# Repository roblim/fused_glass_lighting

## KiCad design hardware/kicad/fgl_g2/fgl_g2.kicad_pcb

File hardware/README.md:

# hardware/

KiCad projects and the scripts that generate and check them. Start with [`../docs/hardware.md`](../docs/hardware.md). For the current board, Rev G2, the decisions are in [`../docs/g2_decisions.md`](../docs/g2_decisions.md).

## Layout

| Path | What |
|---|---|
| `kicad/fgl_g2/` | **Rev G2 controller (current):** `fgl_g2.kicad_pro`/`.kicad_sch`/`.kicad_pcb` (laid out, zones filled), `fgl_g2.pdf`, `fgl_g2.net`, `ERC.rpt`, `DRC.rpt`, `verification.txt`, `bom.csv`, `bom_jlcpcb.csv`, `fgl_g2_layout.png`, `fgl_g2_3d.png`, `fgl_g2_assembly.pdf` (assembly drawing), `fgl.kicad_sym`, `fgl.pretty/` (JILN JL212R port block), and `jlcpcb/` (gerber zip, a BOM + CPL pair for each port variant, DEGSON and JILN, `make_cpl.py`: pad-centre positions and per-LCSC-part rotations checked against JLCPCB's preview) |
| `kicad/fgl_g1/` | Rev G1 controller, superseded 2026-10-23 (KiCad 9, laid out, JLCPCB files in `jlcpcb/`). Kept for reference; don't order |
| `kicad/fgl_rev_f/` | Rev F prototype as built (documentation only; no footprints) |
| `tools/kgen.py` | Small KiCad 7-format schematic writer used by the generators. Supports off-board symbols and per-pin stub lengths |
| `tools/symlib.py` | Project symbols: XIAO ESP32C3, TPS61500, filament port, pot+switch header, LD1500SB, PD trigger, LD2410S, radar and pot headers |
| `tools/gen_g2.py` | Draws the G2 schematic (first version; see Source of truth) |
| `tools/gen_g2_footprints.py` | Writes the Degson terminal footprint into `kicad/fgl_g2/fgl.pretty/` |
| `tools/sepic_design.py` | G2 SEPIC checks (method from TI SLVA904) |
| `tools/gen_g1.py` | Drew the first G1 schematic. Retired |
| `tools/gen_rev_f.py` | Generates the Rev F schematic |
| `tools/g2_expected.py`, `tools/g1_expected.py`, `tools/rev_f_expected.py` | Design intent, written by hand, independent of the generators |
| `tools/verify_pcb.py` | Checks every pad's net on a `.kicad_pcb` against the expected module (`verify_pcb.py board g2_expected`) |
| `tools/verify_netlist.py` | Compares KiCad's exported netlist (s-expression or XML) with the expected one. Also checks no-connects, power sources, footprint pads and BOM fields |
| `tools/schlib.py`, `tools/redraw_g2_sepic.py`, `tools/tidy_g2_labels.py` | Schematic text helpers (pin positions, items in a region, wire/label builders) and the 2026-10-28 clean-up after Flux's review: section 2 (SEPIC) redrawn with wires, label overlaps at JP1/JP2/VBUS_IN/F1/Q2 cleared. Connectivity unchanged |
| `tools/set_datasheets.py` | Fills the Datasheet field of every purchased G2 part (schematic and board) with a direct PDF link, by LCSC number |
| `tools/make_pads_netlist.py` | PADS-PCB netlist (`fgl_g2_pads.asc`) from the KiCad netlist, for tools that don't read KiCad's own format (Pinscope). Same layout as KiCad's PADS export; single-pin nets (unconnected pins) are left out |
| `tools/make_bom.py` | `bom.csv` and `bom_jlcpcb.csv` from the netlist (`make_bom.py net outdir g2_expected` for G2) |
| `tools/power_model.py` | Power and runtime model for Rev F, G1 and G2, inputs listed with sources |
| `tools/layout_g2b/` | Scripts that produced the 90 × 60 mm G2 layout (D19; reference only, the `.kicad_pcb` is the master) |
| `tools/layout_g2/` | Scripts that produced the first, 74 × 58 mm G2 layout (D15; reference only) |
| `tools/make_port_step.py` | Simplified 3D model of the JL212R / DG212R port block (same size) |
| `tools/layout_g1/` | Scripts that produced the G1 layout (reference only) |
| `tools/build.sh` | Exports, verifies (netlist, and the G2 PCB) and rebuilds the BOMs for G2 and G1; runs G2 DRC; regenerates and verifies Rev F |

## Source of truth

**G2:** `kicad/fgl_g2/fgl_g2.kicad_sch` was generated by `gen_g2.py` on 2026-10-23, then saved in KiCad 9.0.7. It is now the master, and `gen_g2.py` refuses to overwrite it unless run with `--force`. Checks:

- **Netlist:** passes `verify_netlist.py` against `g2_expected.py`: 42 nets, 177 connections, 9 no-connects, 74 parts (after the Oct 28 relayout with R29, D19). Mutation tests (JP1 pins 1 and 3 swapped; JP2 pins 1 and 2 swapped; R29 pins swapped) fail as they should.
- **ERC (KiCad 9):** 0 errors. Run through the KiCad MCP's CLI (last on Oct 28) it also lists 69 "footprint not found in library" warnings, one per stock footprint, because that CLI looks for the stock libraries in the wrong folder; `build.sh` with `KiCad.app`'s CLI should give 0 warnings.
- **PCB:** 90 × 60 mm, laid out with `tools/layout_g2b/` (D19 in `g2_decisions.md`; the first 74 × 58 mm layout came from `tools/layout_g2/`, D15). 3D models: the makers' files in `kicad/fgl_g2/3dmodels/`, attached by `tools/set_3d_models.py`. With zones filled, DRC gives 0 errors and 0 unconnected pads. `verify_pcb.py` passes (186 pads, 69 footprints): every pad's net on the board matches `g2_expected.py`.

**G1:** `kicad/fgl_g1/` is frozen as of 2026-10-22, and `gen_g1.py` is retired.

**Rev F:** documentation only. It is still generated by `gen_rev_f.py`.

## Checking after an edit

```
hardware/tools/build.sh
```

This uses KiCad 9's `kicad-cli` from `KiCad.app` (override with `KICAD_CLI`). For G2 and G1 it:

- exports the netlist and PDF
- runs ERC into `ERC.rpt`
- checks the netlist against the expected module
- rewrites the BOMs

It never regenerates G2 or G1.

When you change a circuit, update its `*_expected.py` to match. The verifier will fail until you do. That's deliberate: it is a second, independent statement of what the board should be.

Library paths are found automatically on macOS (`KiCad.app`) and Linux (`/usr/share/kicad`). Override them with `KICAD_SYMBOL_DIR` and `KICAD_FOOTPRINT_DIR`. The G2 TPS61500 footprint (`Package_SO:Texas_HTSSOP-14-1EP…`) exists only in KiCad 9 libraries. On older libraries the verifier uses the pad list recorded in `g2_expected.EXTERNAL_PADS`.

## Not done yet (G2)

These are listed with detail in [`../docs/g2_decisions.md`](../docs/g2_decisions.md#open-items-before-ordering-g2):

- **JLCPCB placement preview:** check every part in the checklist in `docs/hardware.md` (ordering step 3).
- **Header pins against the 5 mm sockets:** 6 mm pins may stop the modules about 2 mm high (D15).
- **Fuse stock.**
- **G2 firmware build.** `src/main.c` has the G2 build (`pio run -e seeed_xiao_esp32c3_g2`), but it has only been compile-checked against the ESP-IDF headers. Build and flash it with PlatformIO. Setup mode, blink codes, keep-alive while lit and the radar UART configuration are still to do.

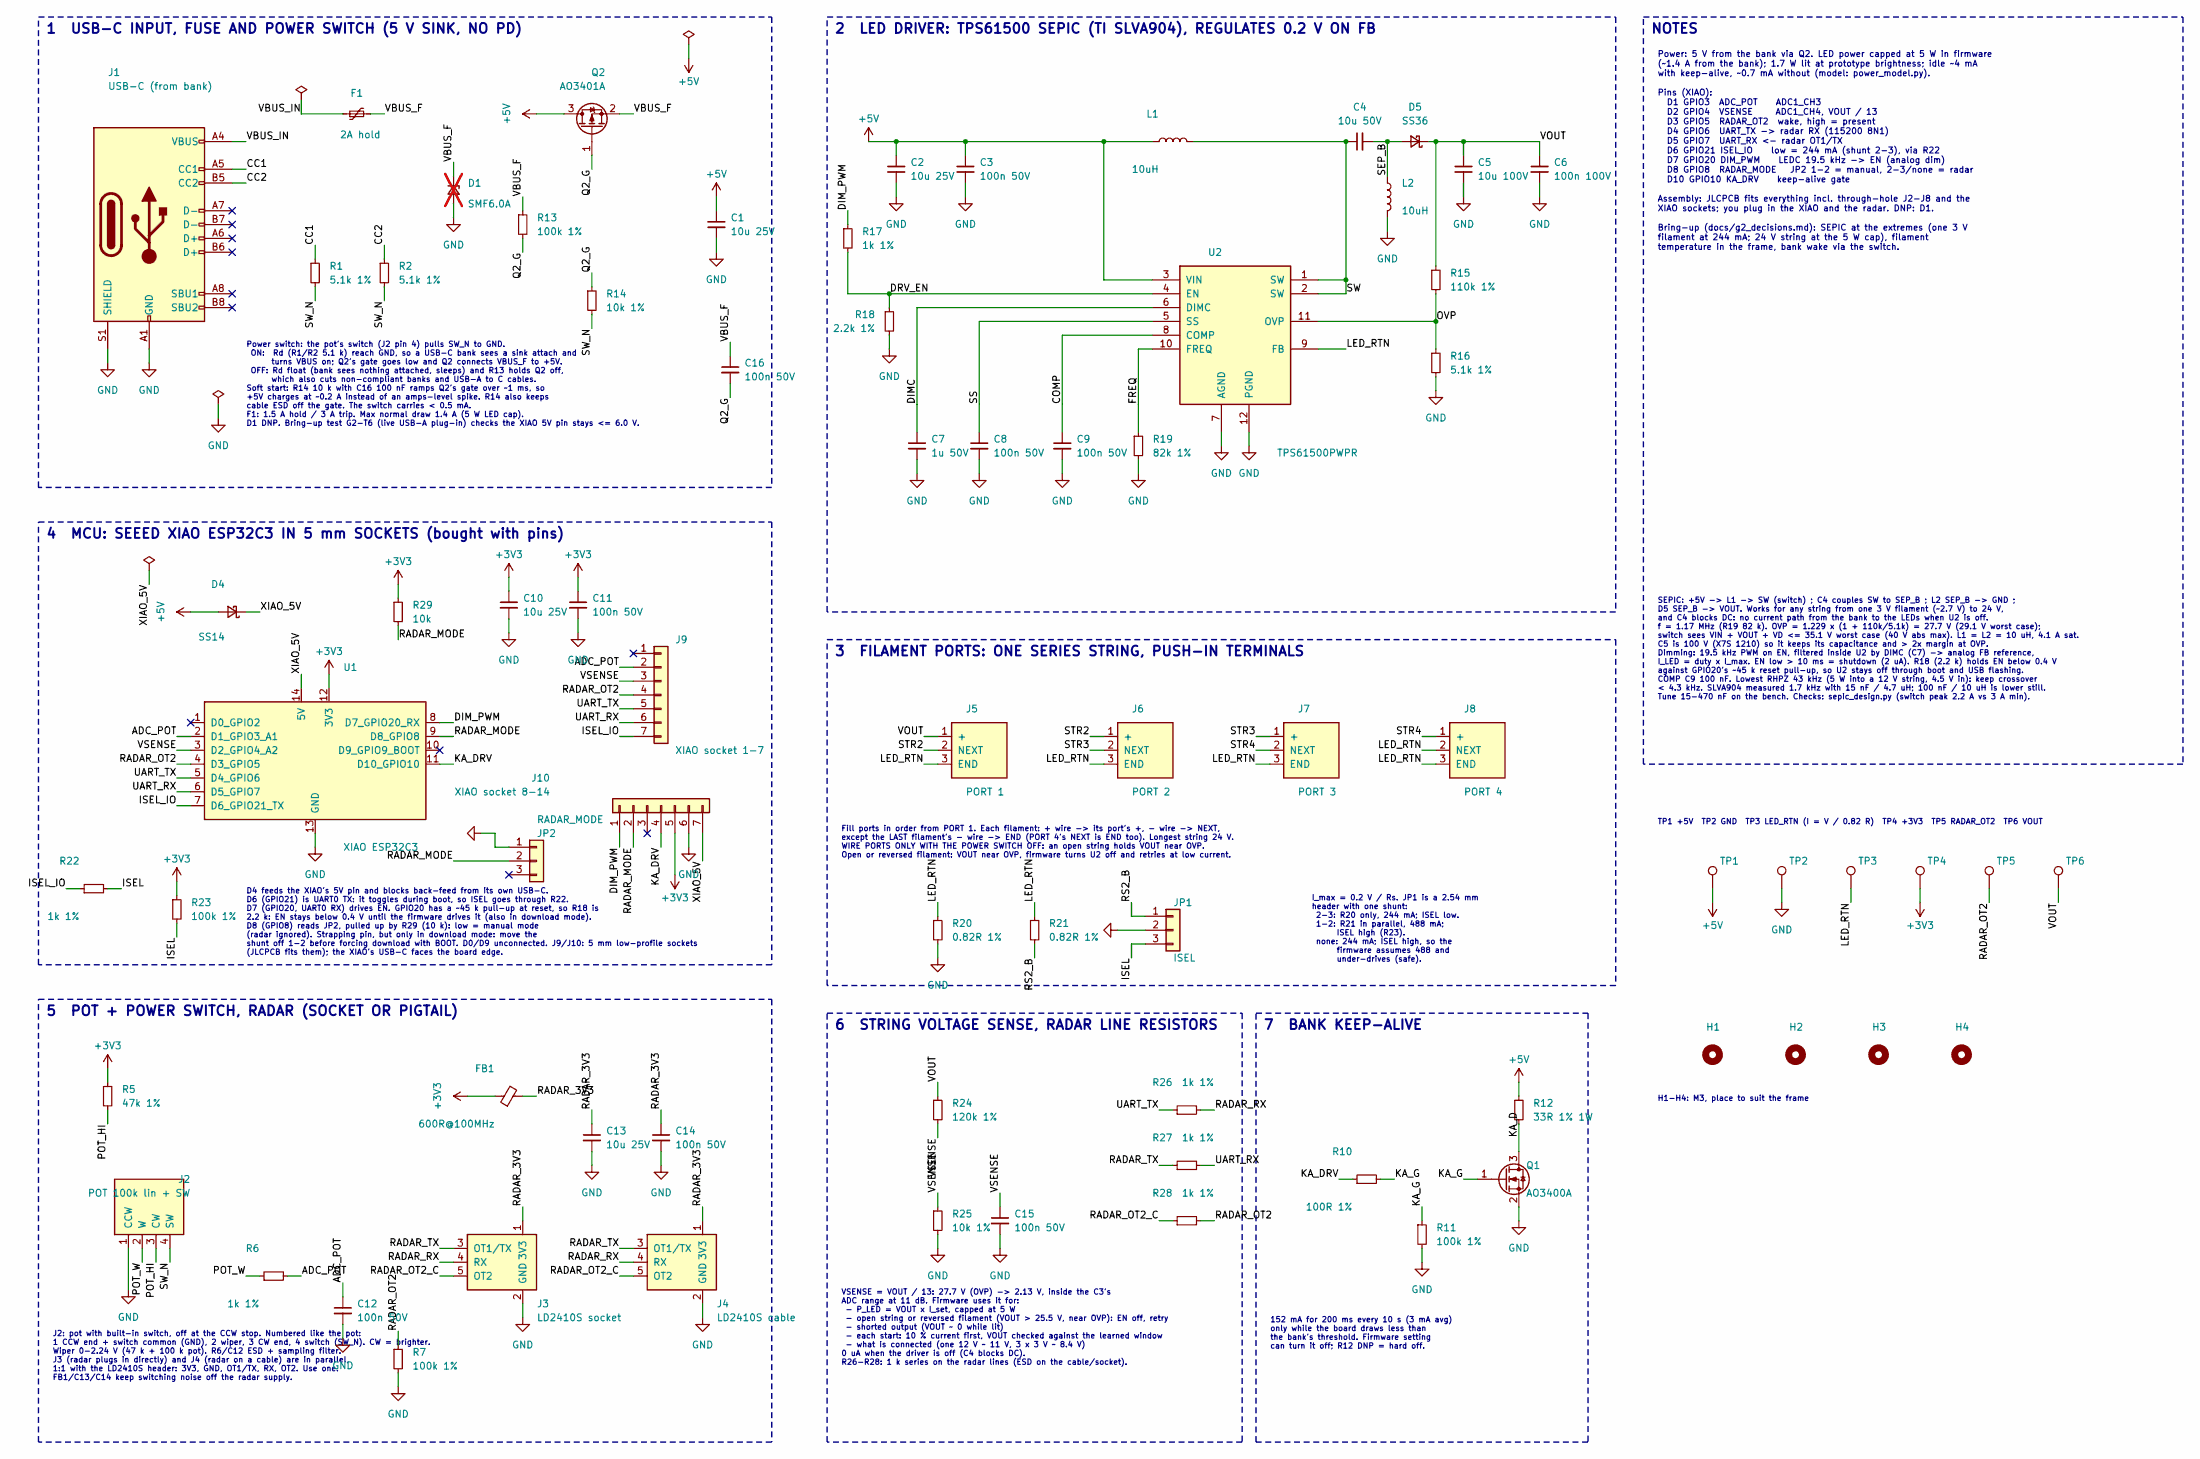
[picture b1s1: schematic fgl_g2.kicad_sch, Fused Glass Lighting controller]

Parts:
C1, C2, C10, C13: 10u 25V; C_0805_2012Metric; MPN CL21A106KAYNNNE; LCSC C15850
C3, C8, C9, C11, C12, C14, C15, C16: 100n 50V; C_0603_1608Metric; MPN CC0603KRX7R9BB104; LCSC C14663
C4: 10u 50V; C_1206_3216Metric; MPN CL31A106KBHNNNE; LCSC C13585
C5: 10u 100V; C_1210_3225Metric; MPN GRM32EC72A106KE05L; LCSC C576517
C6: 100n 100V; C_0603_1608Metric; MPN CL10B104KC8NNNC; LCSC C15725
C7: 1u 50V; C_0603_1608Metric; MPN CL10A105KB8NNNC; LCSC C15849
D1: SMF6.0A; D_SOD-123F; MPN SMF6.0A; LCSC C178260; not fitted
D4: SS14; D_SMA; MPN SS14; LCSC C2480
D5: SS36; D_SMA; MPN SS36; LCSC C2903825
F1: 2A hold; Fuse_1812_4532Metric; MPN SMD1812B200TF/16; LCSC C269145
FB1: 600R@100MHz; L_0603_1608Metric; MPN GZ1608D601TF; LCSC C1002
H1, H2, H3, H4: M3; MountingHole_3.2mm_M3
J1: USB-C (from bank); USB_C_Receptacle_HRO_TYPE-C-31-M-12; MPN TYPE-C-31-M-12; LCSC C165948
J2: POT 100k lin + SW; JST_PH_S4B-PH-K_1x04_P2.00mm_Horizontal; MPN S4B-PH-K-S(LF)(SN); LCSC C157926
J3: LD2410S socket; PinSocket_1x05_P2.54mm_Vertical; MPN HC-PM254-5.0H-1x5PZ; LCSC C27985230
J4: LD2410S cable; JST_PH_S5B-PH-K_1x05_P2.00mm_Horizontal; MPN S5B-PH-K-S(LF)(SN); LCSC C157923
J5: PORT 1; TerminalBlock_JILN_JL212R-3.5-03P_Horizontal; MPN DG212R-THR-3.5-03P-13-1000A(H); LCSC C7603454
J6: PORT 2; TerminalBlock_JILN_JL212R-3.5-03P_Horizontal; MPN DG212R-THR-3.5-03P-13-1000A(H); LCSC C7603454
J7: PORT 3; TerminalBlock_JILN_JL212R-3.5-03P_Horizontal; MPN DG212R-THR-3.5-03P-13-1000A(H); LCSC C7603454
J8: PORT 4; TerminalBlock_JILN_JL212R-3.5-03P_Horizontal; MPN DG212R-THR-3.5-03P-13-1000A(H); LCSC C7603454
J9: XIAO socket 1-7; PinSocket_1x07_P2.54mm_Vertical; MPN HC-PM254-5.0H-1x7PZ; LCSC C27985232
J10: XIAO socket 8-14; PinSocket_1x07_P2.54mm_Vertical; MPN HC-PM254-5.0H-1x7PZ; LCSC C27985232
JP1: ISEL; PinHeader_1x03_P2.54mm_Vertical; MPN 2.54-1*3P; LCSC C49257
JP2: RADAR_MODE; PinHeader_1x03_P2.54mm_Vertical; MPN 2.54-1*3P; LCSC C49257
L1, L2: 10uH; L_Sunlord_SWPA8040S; MPN SWPA8040S100MT; LCSC C37429
Q1: AO3400A; SOT-23; MPN AO3400A; LCSC C20917
Q2: AO3401A; SOT-23; MPN AO3401A; LCSC C15127
R1, R2, R16: 5.1k 1%; R_0603_1608Metric; MPN 0603WAF5101T5E; LCSC C23186
R5: 47k 1%; R_0603_1608Metric; MPN 0603WAF4702T5E; LCSC C25819
R6, R17, R22, R26, R27, R28: 1k 1%; R_0603_1608Metric; MPN 0603WAF1001T5E; LCSC C21190
R7, R11, R13, R23: 100k 1%; R_0603_1608Metric; MPN 0603WAF1003T5E; LCSC C25803
R10: 100R 1%; R_0603_1608Metric; MPN 0603WAF1000T5E; LCSC C22775
R12: 33R 1% 1W; R_2512_6332Metric; MPN 25121WF330JT4E; LCSC C53728
R14, R25: 10k 1%; R_0603_1608Metric; MPN 0603WAF1002T5E; LCSC C25804
R15: 110k 1%; R_0603_1608Metric; MPN 0603WAF1103T5E; LCSC C25805
R18: 2.2k 1%; R_0603_1608Metric; MPN 0603WAF2201T5E; LCSC C4190
R19: 82k 1%; R_0603_1608Metric; MPN 0603WAF8202T5E; LCSC C23254
R20, R21: 0.82R 1%; R_1206_3216Metric; MPN 1206W4F820LT5E; LCSC C30568
R24: 120k 1%; R_0603_1608Metric; MPN 0603WAF1203T5E; LCSC C25808
R29: 10k; R_0603_1608Metric; MPN 0603WAF1002T5E; LCSC C25804
TP1: +5V; TestPoint_Pad_D1.5mm
TP2: GND; TestPoint_Pad_D1.5mm
TP3: LED_RTN; TestPoint_Pad_D1.5mm
TP4: +3V3; TestPoint_Pad_D1.5mm
TP5: RADAR_OT2; TestPoint_Pad_D1.5mm
TP6: VOUT; TestPoint_Pad_D1.5mm
U1: XIAO ESP32C3; MPN 113991054
U2: TPS61500PWPR; Texas_HTSSOP-14-1EP_4.4x5mm_P0.65mm_EP3.4x5mm_Mask3.155x3.2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; MPN TPS61500PWPR; LCSC C71160

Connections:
+3V3: C10.1, C11.1, FB1.1, J10.5, R5.1, R23.1, R29.1, TP4.1, U1.12 (3V3)
+5V: C1.1, C2.1, C3.1, D4.2 (A), L1.1, Q2.3 (D), R12.1, TP1.1, U2.3 (VIN)
/ADC_POT: C12.1, J9.2, R6.2, U1.2 (D1_GPIO3_A1)
/CC1: J1.A5 (CC1), R1.1
/CC2: J1.B5 (CC2), R2.1
/COMP: C9.1, U2.8 (COMP)
/DIMC: C7.1, U2.6 (DIMC)
/DIM_PWM: J10.1, R17.1, U1.8 (D7_GPIO20_RX)
/DRV_EN: R17.2, R18.1, U2.4 (EN)
/FREQ: R19.1, U2.10 (FREQ)
/ISEL: JP1.3, R22.2, R23.2
/ISEL_IO: J9.7, R22.1, U1.7 (D6_GPIO21_TX)
/KA_D: Q1.3 (D), R12.2
/KA_DRV: J10.4, R10.1, U1.11 (D10_GPIO10)
/KA_G: Q1.1 (G), R10.2, R11.1
/LED_RTN: J5.3 (END), J6.3 (END), J7.3 (END), J8.2 (NEXT), J8.3 (END), R20.1, R21.1, TP3.1, U2.9 (FB)
/OVP: R15.2, R16.1, U2.11 (OVP)
/POT_HI: J2.3 (CW), R5.2
/POT_W: J2.2 (W), R6.1
/Q2_G: C16.2, Q2.1 (G), R13.2, R14.1
/RADAR_3V3: C13.1, C14.1, FB1.2, J3.1 (3V3), J4.1 (3V3)
/RADAR_MODE: J10.2, JP2.2, R29.2, U1.9 (D8_GPIO8)
/RADAR_OT2: J9.4, R7.1, R28.2, TP5.1, U1.4 (D3_GPIO5)
/RADAR_OT2_C: J3.5 (OT2), J4.5 (OT2), R28.1
/RADAR_RX: J3.4 (RX), J4.4 (RX), R26.2
/RADAR_TX: J3.3 (OT1/TX), J4.3 (OT1/TX), R27.1
/RS2_B: JP1.1, R21.2
/SEP_B: C4.2, D5.2 (A), L2.1
/SS: C8.1, U2.5 (SS)
/STR2: J5.2 (NEXT), J6.1 (+)
/STR3: J6.2 (NEXT), J7.1 (+)
/STR4: J7.2 (NEXT), J8.1 (+)
/SW: C4.1, L1.2, U2.1 (SW), U2.2 (SW)
/SW_N: J2.4 (SW), R1.2, R2.2, R14.2
/UART_RX: J9.6, R27.2, U1.6 (D5_GPIO7)
/UART_TX: J9.5, R26.1, U1.5 (D4_GPIO6)
/VBUS_F: C16.1, D1.1 (K), F1.2, Q2.2 (S), R13.1
/VBUS_IN: F1.1, J1.A4 (VBUS), J1.A9 (VBUS), J1.B4 (VBUS), J1.B9 (VBUS)
/VOUT: C5.1, C6.1, D5.1 (K), J5.1 (+), R15.1, R24.1, TP6.1
/VSENSE: C15.1, J9.3, R24.2, R25.1, U1.3 (D2_GPIO4_A2)
/XIAO_5V: D4.1 (K), J10.7, U1.14 (5V)
GND: C1.2, C2.2, C3.2, C5.2, C6.2, C7.2, C8.2, C9.2, C10.2, C11.2, C12.2, C13.2, C14.2, C15.2, D1.2 (A), J1.A1 (GND), J1.A12 (GND), J1.B1 (GND), J1.B12 (GND), J1.S1 (SHIELD), J2.1 (CCW), J3.2 (GND), J4.2 (GND), J10.6, JP1.2, JP2.1, L2.2, Q1.2 (S), R7.2, R11.2, R16.2, R18.2, R19.2, R20.2, R25.2, TP2.1, U1.13 (GND), U2.7 (AGND), U2.12 (PGND), U2.13 (PGND), U2.14 (PGND), U2.15 (EP)

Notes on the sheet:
H1-H4: M3, place to suit the frame
1 USB-C INPUT, FUSE AND POWER SWITCH (5 V SINK, NO PD)
7 BANK KEEP-ALIVE
2 LED DRIVER: TPS61500 SEPIC (TI SLVA904), REGULATES 0.2 V ON FB
TP1 +5V TP2 GND TP3 LED_RTN (I = V / 0.82 R) TP4 +3V3 TP5 RADAR_OT2 TP6 VOUT
3 FILAMENT PORTS: ONE SERIES STRING, PUSH-IN TERMINALS
152 mA for 200 ms every 10 s (3 mA avg) only while the board draws less than the bank's threshold. Firmware setting can turn it off; R12 DNP = hard off.
VSENSE = VOUT / 13: 27.7 V (OVP) -> 2.13 V, inside the C3's ADC range at 11 dB. Firmware uses it for: - P_LED = VOUT x I_set, capped at 5 W - open string or reversed filament (VOUT > 25.5 V, near OVP): EN off, retry - shorted output (VOUT ~ 0 while lit) - each start: 10 % current first, VOUT checke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
5 POT + POWER SWITCH, RADAR (SOCKET OR PIGTAIL)
D4 feeds the XIAO's 5V pin and blocks back-feed from its own USB-C. D6 (GPIO21) is UART0 TX: it toggles during boot, so ISEL goes through R22. D7 (GPIO20, UART0 RX) drives EN. GPIO20 has a ~45 k pull-up at reset, so R18 is 2.2 k: EN stays below 0.4 V until the firmware drives it (also in download m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
6 STRING VOLTAGE SENSE, RADAR LINE RESISTORS
Power: 5 V from the bank via Q2. LED power capped at 5 W in firmware (~1.4 A from the bank); 1.7 W lit at prototype brightness; idle ~4 mA with keep-alive, ~0.7 mA without (model: power_model.py). Pins (XIAO): D1 GPIO3 ADC_POT ADC1_CH3 D2 GPIO4 VSENSE ADC1_CH4, VOUT / 13 D3 GPIO5 RADAR_OT2 wake, hi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
SEPIC: +5V -> L1 -> SW (switch) ; C4 couples SW to SEP_B ; L2 SEP_B -> GND ; D5 SEP_B -> VOUT. Works for any string from one 3 V filament (~2.7 V) to 24 V, and C4 blocks DC: no current path from the bank to the LEDs when U2 is off. f = 1.17 MHz (R19 82 k). OVP = 1.229 x (1 + 110k/5.1k) = 27.7 V (29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
Fill ports in order from PORT 1. Each filament: + wire -> its port's +, - wire -> NEXT, except the LAST filament's - wire -> END (PORT 4's NEXT is END too). Longest string 24 V. WIRE PORTS ONLY WITH THE POWER SWITCH OFF: an open string holds VOUT near OVP. Open or reversed filament: VOUT near OVP, 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
NOTES
I_max = 0.2 V / Rs. JP1 is a 2.54 mm header with one shunt: 2-3: R20 only, 244 mA; ISEL low. 1-2: R21 in parallel, 488 mA; ISEL high (R23). none: 244 mA; ISEL high, so the firmware assumes 488 and under-drives (safe).
4 MCU: SEEED XIAO ESP32C3 IN 5 mm SOCKETS (bought with pins)
J2: pot with built-in switch, off at the CCW stop. Numbered like the pot: 1 CCW end + switch common (GND), 2 wiper, 3 CW end, 4 switch (SW_N). CW = brighter. Wiper 0-2.24 V (47 k + 100 k pot). R6/C12 ESD + sampling filter. J3 (radar plugs in directly) and J4 (radar on a cable) are in parallel, 1:1 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
Power switch: the pot's switch (J2 pin 4) pulls SW_N to GND. ON: Rd (R1/R2 5.1 k) reach GND, so a USB-C bank sees a sink attach and turns VBUS on; Q2's gate goes low and Q2 connects VBUS_F to +5V. OFF: Rd float (bank sees nothing attached, sleeps) and R13 holds Q2 off, which also cuts non-compliant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

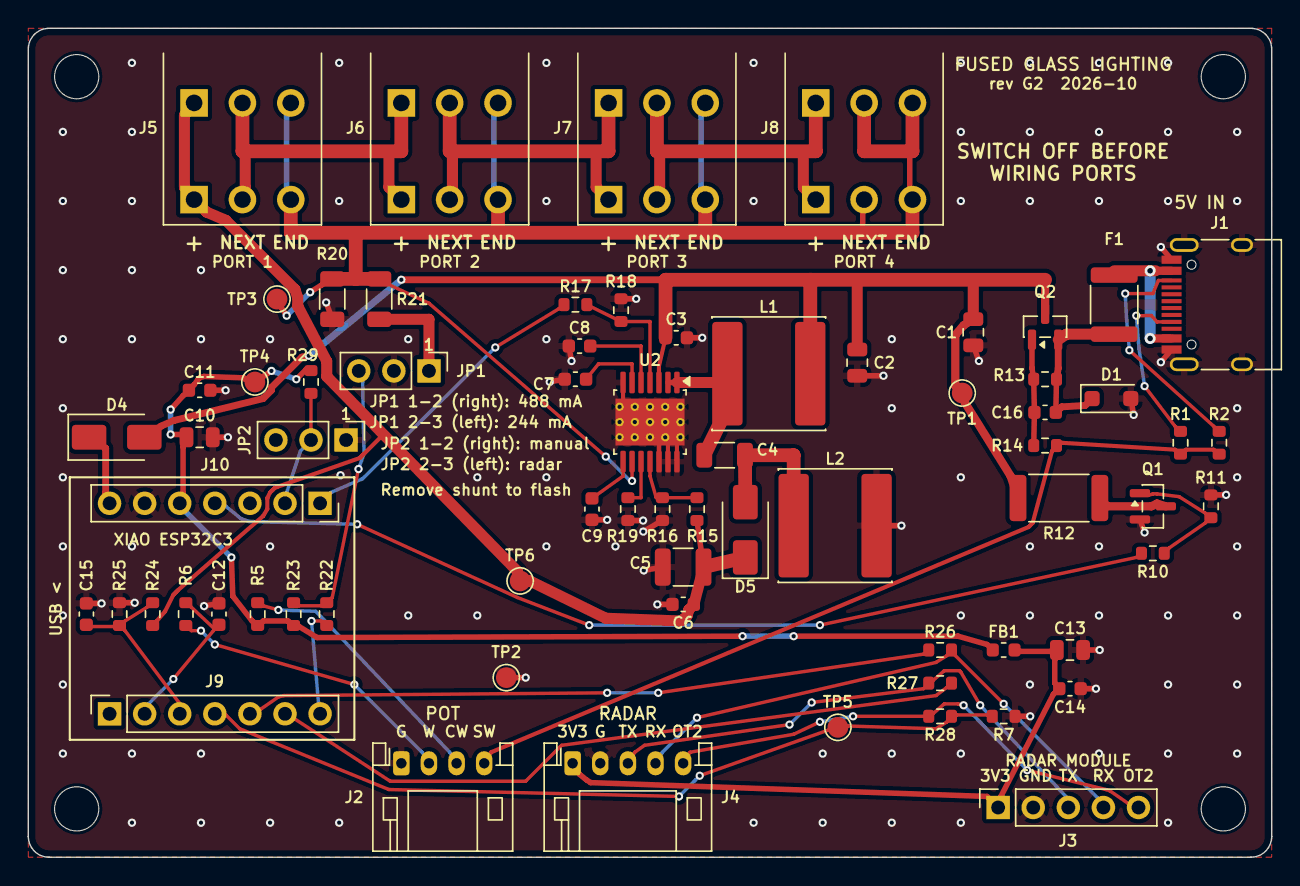
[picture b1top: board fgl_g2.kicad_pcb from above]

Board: 2 copper layers, 90.0 x 60.0 mm, 73 parts (0 on the bottom side), 42 nets.

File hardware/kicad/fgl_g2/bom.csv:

Qty,References,Value,Footprint,MPN,Manufacturer,LCSC,Assembly
4,"C1,C2,C10,C13",10u 25V,C_0805_2012Metric,CL21A106KAYNNNE,Samsung,C15850,JLCPCB
8,"C3,C8,C9,C11,C12,C14,C15,C16",100n 50V,C_0603_1608Metric,CC0603KRX7R9BB104,YAGEO,C14663,JLCPCB
1,C4,10u 50V,C_1206_3216Metric,CL31A106KBHNNNE,Samsung,C13585,JLCPCB
1,C5,10u 100V,C_1210_3225Metric,GRM32EC72A106KE05L,Murata,C576517,JLCPCB
1,C6,100n 100V,C_0603_1608Metric,CL10B104KC8NNNC,Samsung,C15725,JLCPCB
1,C7,1u 50V,C_0603_1608Metric,CL10A105KB8NNNC,Samsung,C15849,JLCPCB
1,D1,SMF6.0A,D_SOD-123F,SMF6.0A,Jingdao,C178260,DNP
1,D4,SS14,D_SMA,SS14,MDD,C2480,JLCPCB
1,D5,SS36,D_SMA,SS36,LGE,C2903825,JLCPCB
1,F1,2A hold,Fuse_1812_4532Metric,SMD1812B200TF/16,Brightking,C269145,JLCPCB
1,FB1,600R@100MHz,L_0603_1608Metric,GZ1608D601TF,Sunlord,C1002,JLCPCB
1,J1,USB-C (from bank),USB_C_Receptacle_HRO_TYPE-C-31-M-12,TYPE-C-31-M-12,Korean Hroparts Elec,C165948,JLCPCB
1,J2,POT 100k lin + SW,JST_PH_S4B-PH-K_1x04_P2.00mm_Horizontal,S4B-PH-K-S(LF)(SN),JST,C157926,JLCPCB
1,J3,LD2410S socket,PinSocket_1x05_P2.54mm_Vertical,HC-PM254-5.0H-1x5PZ,Hong Cheng,C27985230,JLCPCB
1,J4,LD2410S cable,JST_PH_S5B-PH-K_1x05_P2.00mm_Horizontal,S5B-PH-K-S(LF)(SN),JST,C157923,JLCPCB
1,J5,PORT 1,TerminalBlock_JILN_JL212R-3.5-03P_Horizontal,DG212R-THR-3.5-03P-13-1000A(H),DEGSON,C7603454,JLCPCB
1,J6,PORT 2,TerminalBlock_JILN_JL212R-3.5-03P_Horizontal,DG212R-THR-3.5-03P-13-1000A(H),DEGSON,C7603454,JLCPCB
1,J7,PORT 3,TerminalBlock_JILN_JL212R-3.5-03P_Horizontal,DG212R-THR-3.5-03P-13-1000A(H),DEGSON,C7603454,JLCPCB
1,J8,PORT 4,TerminalBlock_JILN_JL212R-3.5-03P_Horizontal,DG212R-THR-3.5-03P-13-1000A(H),DEGSON,C7603454,JLCPCB
1,J9,XIAO socket 1-7,PinSocket_1x07_P2.54mm_Vertical,HC-PM254-5.0H-1x7PZ,Hong Cheng,C27985232,JLCPCB
1,J10,XIAO socket 8-14,PinSocket_1x07_P2.54mm_Vertical,HC-PM254-5.0H-1x7PZ,Hong Cheng,C27985232,JLCPCB
1,JP1,ISEL,PinHeader_1x03_P2.54mm_Vertical,2.54-1*3P,BOOMELE,C49257,JLCPCB
2,"JP1-shunt, JP2-shunt",2.54 mm shunt for JP1 / JP2,"(loose part, open top)",2.54,BOOMELE,C5305,loose
1,JP2,RADAR_MODE,PinHeader_1x03_P2.54mm_Vertical,2.54-1*3P,BOOMELE,C49257,JLCPCB
2,"L1,L2",10uH,L_Sunlord_SWPA8040S,SWPA8040S100MT,Sunlord,C37429,JLCPCB
1,Q1,AO3400A,SOT-23,AO3400A,AOS,C20917,JLCPCB
1,Q2,AO3401A,SOT-23,AO3401A,AOS,C15127,JLCPCB
3,"R1,R2,R16",5.1k 1%,R_0603_1608Metric,0603WAF5101T5E,UNI-ROYAL,C23186,JLCPCB
1,R5,47k 1%,R_0603_1608Metric,0603WAF4702T5E,UNI-ROYAL,C25819,JLCPCB
6,"R6,R17,R22,R26,R27,R28",1k 1%,R_0603_1608Metric,0603WAF1001T5E,UNI-ROYAL,C21190,JLCPCB
4,"R7,R11,R13,R23",100k 1%,R_0603_1608Metric,0603WAF1003T5E,UNI-ROYAL,C25803,JLCPCB
1,R10,100R 1%,R_0603_1608Metric,0603WAF1000T5E,UNI-ROYAL,C22775,JLCPCB
1,R12,33R 1% 1W,R_2512_6332Metric,25121WF330JT4E,UNI-ROYAL,C53728,JLCPCB
2,"R14,R25",10k 1%,R_0603_1608Metric,0603WAF1002T5E,UNI-ROYAL,C25804,JLCPCB
1,R15,110k 1%,R_0603_1608Metric,0603WAF1103T5E,UNI-ROYAL,C25805,JLCPCB
1,R18,2.2k 1%,R_0603_1608Metric,0603WAF2201T5E,UNI-ROYAL,C4190,JLCPCB
1,R19,82k 1%,R_0603_1608Metric,0603WAF8202T5E,UNI-ROYAL,C23254,JLCPCB
2,"R20,R21",0.82R 1%,R_1206_3216Metric,1206W4F820LT5E,UNI-ROYAL,C30568,JLCPCB
1,R24,120k 1%,R_0603_1608Metric,0603WAF1203T5E,UNI-ROYAL,C25808,JLCPCB
1,R29,10k,R_0603_1608Metric,0603WAF1002T5E,UNI-ROYAL,C25804,JLCPCB
1,U1,XIAO ESP32C3,(plugs into J9/J10; order with pre-soldered headers),113991054,Seeed Studio,,hand
1,U2,TPS61500PWPR,Texas_HTSSOP-14-1EP_4.4x5mm_P0.65mm_EP3.4x5mm_Mask3.155x3.255mm_ThermalVias,TPS61500PWPR,TI,C71160,JLCPCB

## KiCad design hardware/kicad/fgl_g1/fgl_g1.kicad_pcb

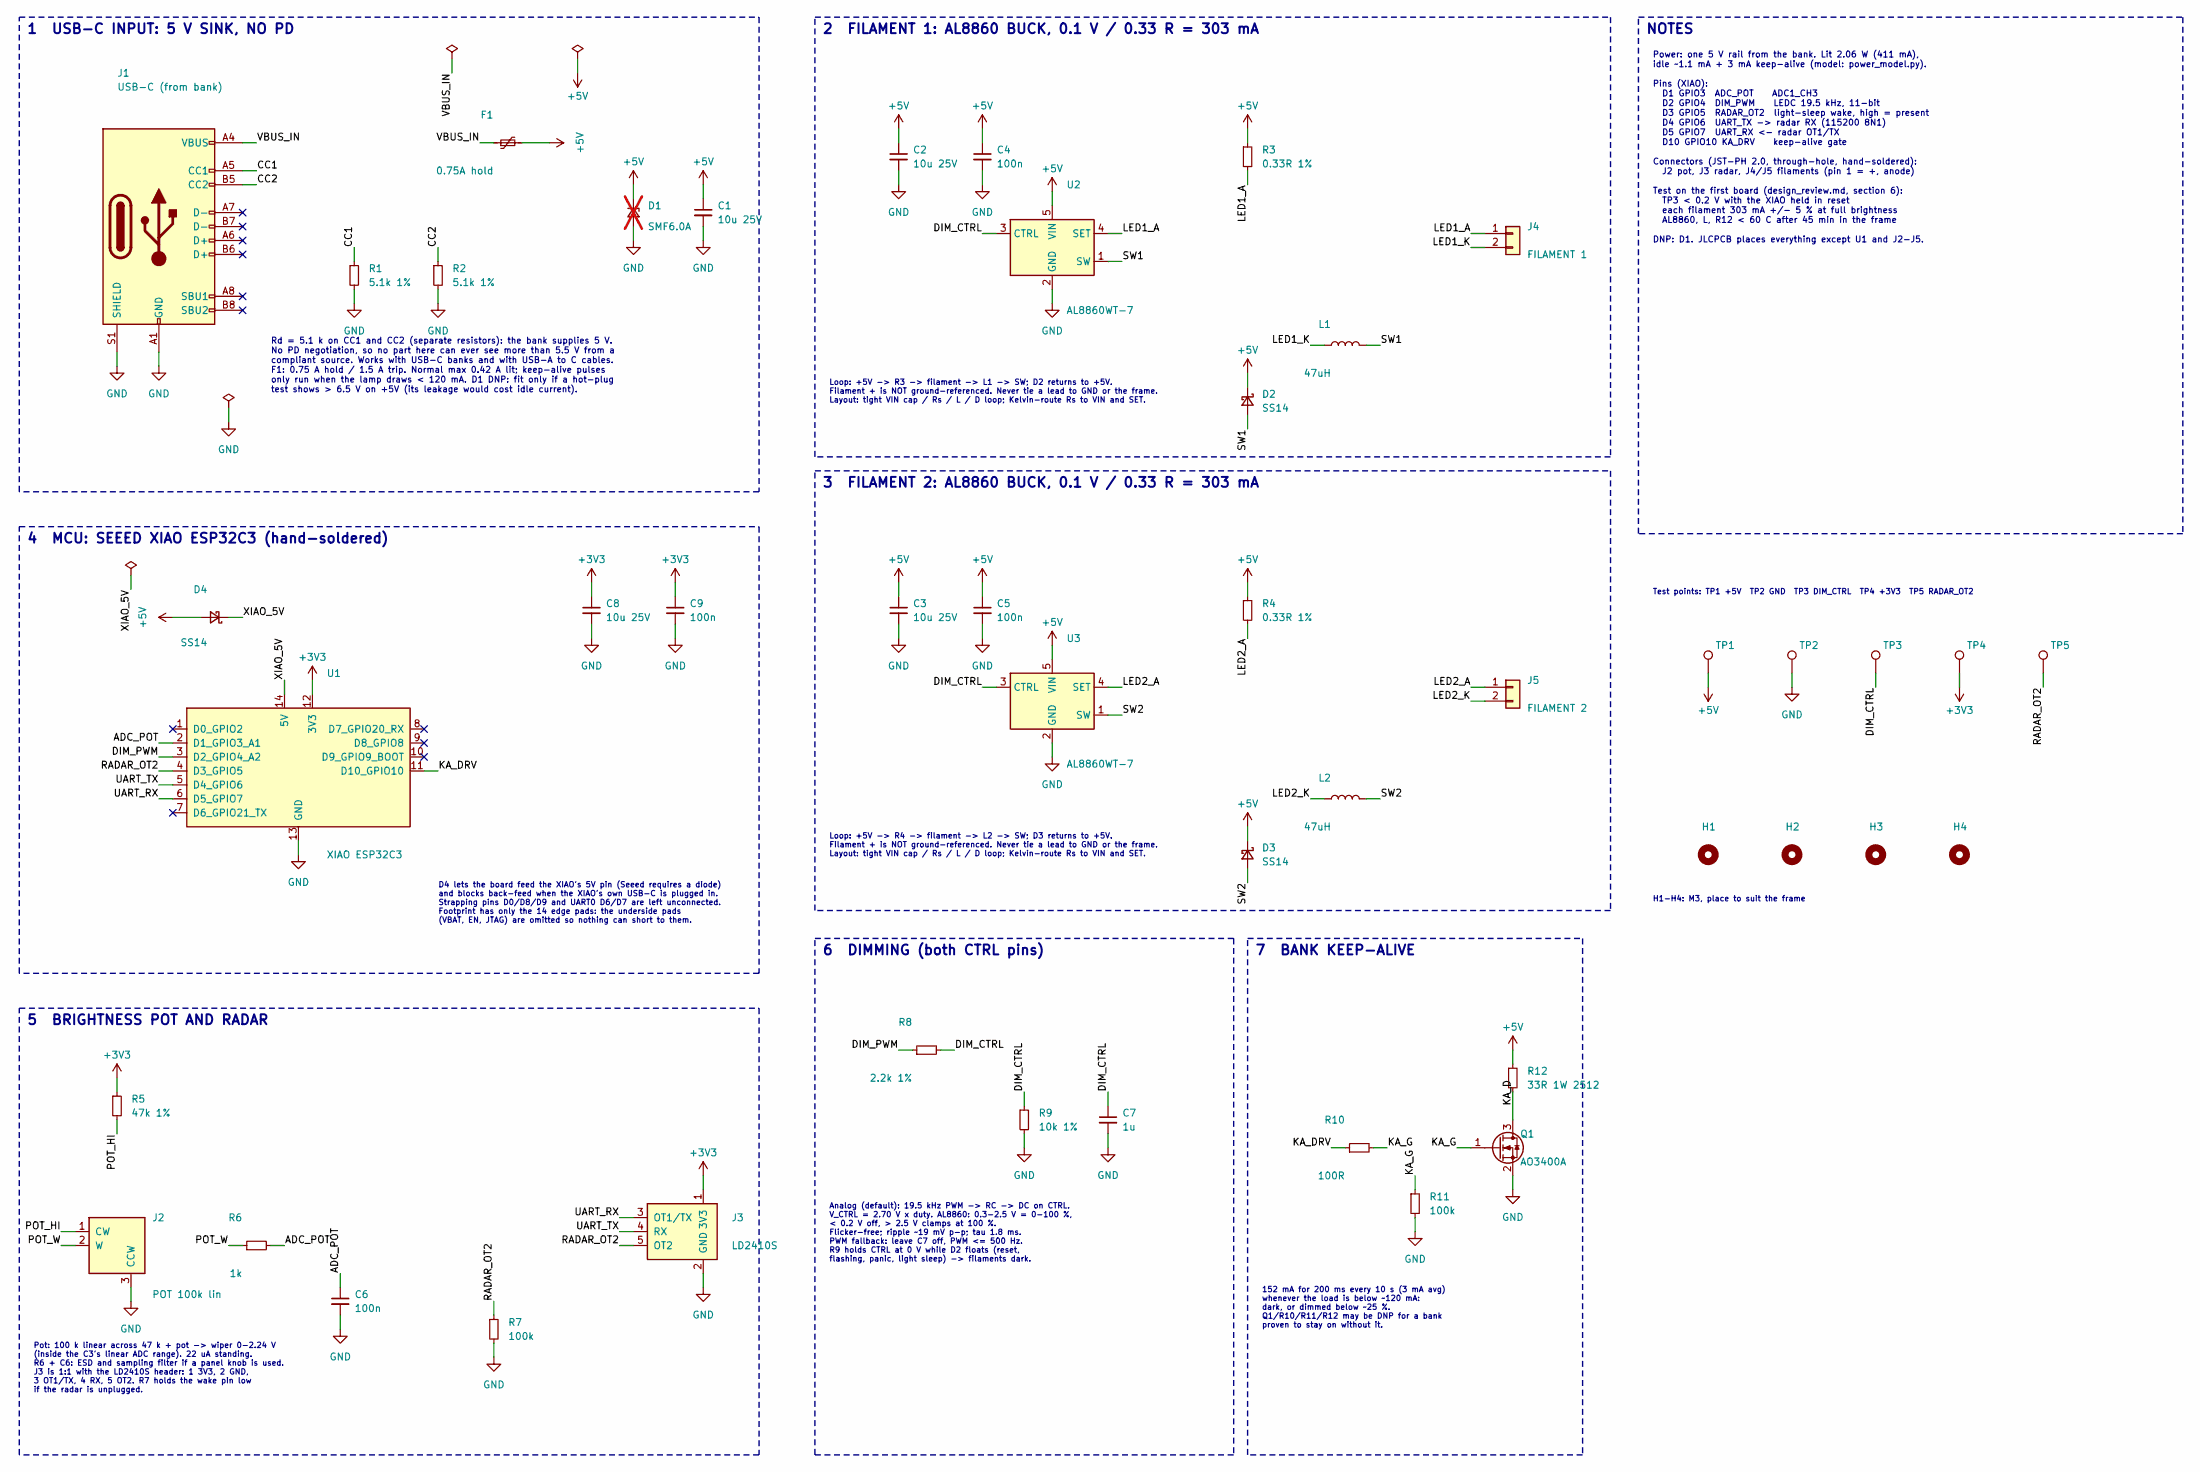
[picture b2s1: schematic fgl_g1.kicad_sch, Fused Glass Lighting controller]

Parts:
C1, C2, C3, C8: 10u 25V; C_0805_2012Metric; MPN CL21A106KAYNNNE; LCSC C15850
C4, C5, C6, C9: 100n; C_0603_1608Metric; MPN CC0603KRX7R9BB104; LCSC C14663
C7: 1u; C_0603_1608Metric; MPN CL10A105KB8NNNC; LCSC C15849
D1: SMF6.0A; D_SOD-123F; MPN SMF6.0A; LCSC C178260; not fitted
D2, D3, D4: SS14; D_SMA; MPN SS14; LCSC C2480
F1: 0.75A hold; Fuse_1206_3216Metric; MPN 1206L075THYR; LCSC C99563
H1, H2, H3, H4: M3; MountingHole_3.2mm_M3
J1: USB-C (from bank); USB_C_Receptacle_HRO_TYPE-C-31-M-12; MPN TYPE-C-31-M-12; LCSC C165948
J2: POT 100k lin; JST_PH_S3B-PH-K_1x03_P2.00mm_Horizontal; MPN S3B-PH-K-S(LF)(SN); LCSC C157929
J3: LD2410S; JST_PH_S5B-PH-K_1x05_P2.00mm_Horizontal; MPN S5B-PH-K-S(LF)(SN); LCSC C157923
J4: FILAMENT 1; JST_PH_S2B-PH-K_1x02_P2.00mm_Horizontal; MPN S2B-PH-K-S(LF)(SN); LCSC C173752
J5: FILAMENT 2; JST_PH_S2B-PH-K_1x02_P2.00mm_Horizontal; MPN S2B-PH-K-S(LF)(SN); LCSC C173752
L1, L2: 47uH; L_Sunlord_SWPA6045S; MPN SWPA6045S470MT; LCSC C36414
Q1: AO3400A; SOT-23; MPN AO3400A; LCSC C20917
R1, R2: 5.1k 1%; R_0603_1608Metric; MPN 0603WAF5101T5E; LCSC C23186
R3, R4: 0.33R 1%; R_1206_3216Metric; MPN 1206W4F330LT5E; LCSC C25337
R5: 47k 1%; R_0603_1608Metric; MPN 0603WAF4702T5E; LCSC C25819
R6: 1k; R_0603_1608Metric; MPN 0603WAF1001T5E; LCSC C21190
R7, R11: 100k; R_0603_1608Metric; MPN 0603WAF1003T5E; LCSC C25803
R8: 2.2k 1%; R_0603_1608Metric; MPN 0603WAF2201T5E; LCSC C4190
R9: 10k 1%; R_0603_1608Metric; MPN 0603WAF1002T5E; LCSC C25804
R10: 100R; R_0603_1608Metric; MPN 0603WAF1000T5E; LCSC C22775
R12: 33R 1W 2512; R_2512_6332Metric; MPN 25121WF330JT4E; LCSC C53728
TP1: +5V; TestPoint_Pad_D1.5mm
TP2: GND; TestPoint_Pad_D1.5mm
TP3: DIM_CTRL; TestPoint_Pad_D1.5mm
TP4: +3V3; TestPoint_Pad_D1.5mm
TP5: RADAR_OT2; TestPoint_Pad_D1.5mm
U1: XIAO ESP32C3; XIAO_ESP32C3_Castellated; MPN 113991054
U2, U3: AL8860WT-7; TSOT-23-5; MPN AL8860WT-7; LCSC C125330

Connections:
+3V3: C8.1, C9.1, J3.1 (3V3), R5.1, TP4.1, U1.12 (3V3)
+5V: C1.1, C2.1, C3.1, C4.1, C5.1, D1.1 (K), D2.1 (K), D3.1 (K), D4.2 (A), F1.2, R3.1, R4.1, R12.1, TP1.1, U2.5 (VIN), U3.5 (VIN)
/ADC_POT: C6.1, R6.2, U1.2 (D1_GPIO3_A1)
/CC1: J1.A5 (CC1), R1.1
/CC2: J1.B5 (CC2), R2.1
/DIM_CTRL: C7.1, R8.2, R9.1, TP3.1, U2.3 (CTRL), U3.3 (CTRL)
/DIM_PWM: R8.1, U1.3 (D2_GPIO4_A2)
/KA_D: Q1.3 (D), R12.2
/KA_DRV: R10.1, U1.11 (D10_GPIO10)
/KA_G: Q1.1 (G), R10.2, R11.1
/LED1_A: J4.1, R3.2, U2.4 (SET)
/LED1_K: J4.2, L1.1
/LED2_A: J5.1, R4.2, U3.4 (SET)
/LED2_K: J5.2, L2.1
/POT_HI: J2.1 (CW), R5.2
/POT_W: J2.2 (W), R6.1
/RADAR_OT2: J3.5 (OT2), R7.1, TP5.1, U1.4 (D3_GPIO5)
/SW1: D2.2 (A), L1.2, U2.1 (SW)
/SW2: D3.2 (A), L2.2, U3.1 (SW)
/UART_RX: J3.3 (OT1/TX), U1.6 (D5_GPIO7)
/UART_TX: J3.4 (RX), U1.5 (D4_GPIO6)
/VBUS_IN: F1.1, J1.A4 (VBUS), J1.A9 (VBUS), J1.B4 (VBUS), J1.B9 (VBUS)
/XIAO_5V: D4.1 (K), U1.14 (5V)
GND: C1.2, C2.2, C3.2, C4.2, C5.2, C6.2, C7.2, C8.2, C9.2, D1.2 (A), J1.A1 (GND), J1.A12 (GND), J1.B1 (GND), J1.B12 (GND), J1.S1 (SHIELD), J2.3 (CCW), J3.2 (GND), Q1.2 (S), R1.2, R2.2, R7.2, R9.2, R11.2, TP2.1, U1.13 (GND), U2.2 (GND), U3.2 (GND)

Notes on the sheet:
NOTES
3 FILAMENT 2: AL8860 BUCK, 0.1 V / 0.33 R = 303 mA
1 USB-C INPUT: 5 V SINK, NO PD
Test points: TP1 +5V TP2 GND TP3 DIM_CTRL TP4 +3V3 TP5 RADAR_OT2
Rd = 5.1 k on CC1 and CC2 (separate resistors): the bank supplies 5 V. No PD negotiation, so no part here can ever see more than 5.5 V from a compliant source. Works with USB-C banks and with USB-A to C cables. F1: 0.75 A hold / 1.5 A trip. Normal max 0.42 A lit; keep-alive pulses only run when the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
D4 lets the board feed the XIAO's 5V pin (Seeed requires a diode) and blocks back-feed when the XIAO's own USB-C is plugged in. Strapping pins D0/D8/D9 and UART0 D6/D7 are left unconnected. Footprint has only the 14 edge pads: the underside pads (VBAT, EN, JTAG) are omitted so nothing can short to 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
H1-H4: M3, place to suit the frame
Power: one 5 V rail from the bank. Lit 2.06 W (411 mA), idle ~1.1 mA + 3 mA keep-alive (model: power_model.py). Pins (XIAO): D1 GPIO3 ADC_POT ADC1_CH3 D2 GPIO4 DIM_PWM LEDC 19.5 kHz, 11-bit D3 GPIO5 RADAR_OT2 light-sleep wake, high = present D4 GPIO6 UART_TX -> radar RX (115200 8N1) D5 GPIO7 UART_R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
5 BRIGHTNESS POT AND RADAR
4 MCU: SEEED XIAO ESP32C3 (hand-soldered)
7 BANK KEEP-ALIVE
Loop: +5V -> R4 -> filament -> L2 -> SW; D3 returns to +5V. Filament + is NOT ground-referenced. Never tie a lead to GND or the frame. Layout: tight VIN cap / Rs / L / D loop; Kelvin-route Rs to VIN and SET.
Analog (default): 19.5 kHz PWM -> RC -> DC on CTRL. V_CTRL = 2.70 V x duty. AL8860: 0.3-2.5 V = 0-100 %, < 0.2 V off, > 2.5 V clamps at 100 %. Flicker-free; ripple ~19 mV p-p; tau 1.8 ms. PWM fallback: leave C7 off, PWM <= 500 Hz. R9 holds CTRL at 0 V while D2 floats (reset, flashing, panic, light 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
152 mA for 200 ms every 10 s (3 mA avg) whenever the load is below ~120 mA: dark, or dimmed below ~25 %. Q1/R10/R11/R12 may be DNP for a bank proven to stay on without it.
Loop: +5V -> R3 -> filament -> L1 -> SW; D2 returns to +5V. Filament + is NOT ground-referenced. Never tie a lead to GND or the frame. Layout: tight VIN cap / Rs / L / D loop; Kelvin-route Rs to VIN and SET.
Pot: 100 k linear across 47 k + pot -> wiper 0-2.24 V (inside the C3's linear ADC range). 22 uA standing. R6 + C6: ESD and sampling filter if a panel knob is used. J3 is 1:1 with the LD2410S header: 1 3V3, 2 GND, 3 OT1/TX, 4 RX, 5 OT2. R7 holds the wake pin low if the radar is unplugged.
2 FILAMENT 1: AL8860 BUCK, 0.1 V / 0.33 R = 303 mA
6 DIMMING (both CTRL pins)

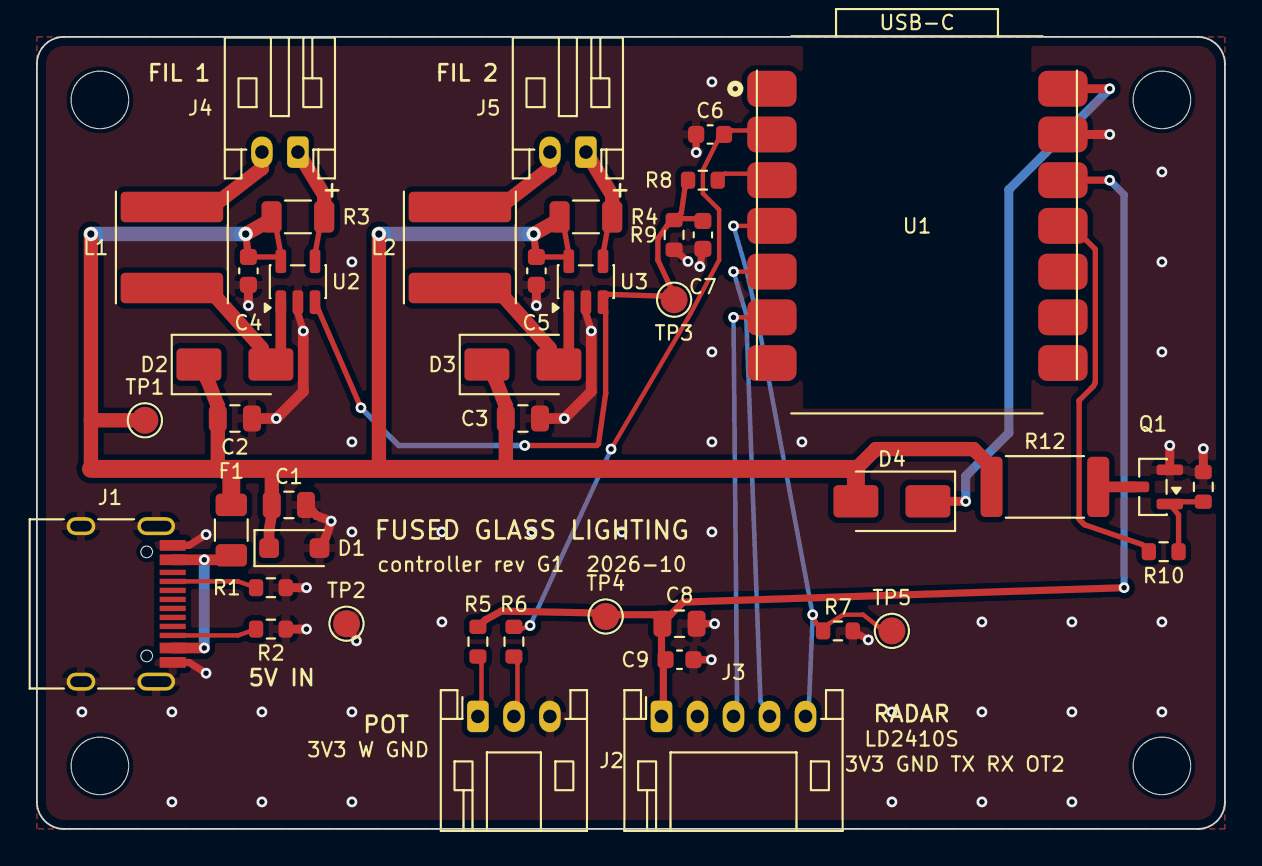
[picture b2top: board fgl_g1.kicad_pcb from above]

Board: 2 copper layers, 66.0 x 44.0 mm, 46 parts (0 on the bottom side), 24 nets.

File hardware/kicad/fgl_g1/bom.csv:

Qty,References,Value,Footprint,MPN,Manufacturer,LCSC,Assembly
4,"C1,C2,C3,C8",10u 25V,C_0805_2012Metric,CL21A106KAYNNNE,Samsung,C15850,JLCPCB
4,"C4,C5,C6,C9",100n,C_0603_1608Metric,CC0603KRX7R9BB104,YAGEO,C14663,JLCPCB
1,C7,1u,C_0603_1608Metric,CL10A105KB8NNNC,Samsung,C15849,JLCPCB
1,D1,SMF6.0A,D_SOD-123F,SMF6.0A,Jingdao,C178260,DNP
3,"D2,D3,D4",SS14,D_SMA,SS14,MDD,C2480,JLCPCB
1,F1,0.75A hold,Fuse_1206_3216Metric,1206L075THYR,Littelfuse,C99563,JLCPCB
1,J1,USB-C (from bank),USB_C_Receptacle_HRO_TYPE-C-31-M-12,TYPE-C-31-M-12,Korean Hroparts Elec,C165948,JLCPCB
1,J2,POT 100k lin,JST_PH_S3B-PH-K_1x03_P2.00mm_Horizontal,S3B-PH-K-S(LF)(SN),JST,C157929,hand
1,J3,LD2410S,JST_PH_S5B-PH-K_1x05_P2.00mm_Horizontal,S5B-PH-K-S(LF)(SN),JST,C157923,hand
1,J4,FILAMENT 1,JST_PH_S2B-PH-K_1x02_P2.00mm_Horizontal,S2B-PH-K-S(LF)(SN),JST,C173752,hand
1,J5,FILAMENT 2,JST_PH_S2B-PH-K_1x02_P2.00mm_Horizontal,S2B-PH-K-S(LF)(SN),JST,C173752,hand
2,"L1,L2",47uH,L_Sunlord_SWPA6045S,SWPA6045S470MT,Sunlord,C36414,JLCPCB
1,Q1,AO3400A,SOT-23,AO3400A,AOS,C20917,JLCPCB
2,"R1,R2",5.1k 1%,R_0603_1608Metric,0603WAF5101T5E,UNI-ROYAL,C23186,JLCPCB
2,"R3,R4",0.33R 1%,R_1206_3216Metric,1206W4F330LT5E,UNI-ROYAL,C25337,JLCPCB
1,R5,47k 1%,R_0603_1608Metric,0603WAF4702T5E,UNI-ROYAL,C25819,JLCPCB
1,R6,1k,R_0603_1608Metric,0603WAF1001T5E,UNI-ROYAL,C21190,JLCPCB
2,"R7,R11",100k,R_0603_1608Metric,0603WAF1003T5E,UNI-ROYAL,C25803,JLCPCB
1,R8,2.2k 1%,R_0603_1608Metric,0603WAF2201T5E,UNI-ROYAL,C4190,JLCPCB
1,R9,10k 1%,R_0603_1608Metric,0603WAF1002T5E,UNI-ROYAL,C25804,JLCPCB
1,R10,100R,R_0603_1608Metric,0603WAF1000T5E,UNI-ROYAL,C22775,JLCPCB
1,R12,33R 1W 2512,R_2512_6332Metric,25121WF330JT4E,UNI-ROYAL,C53728,JLCPCB
1,U1,XIAO ESP32C3,XIAO_ESP32C3_Castellated,113991054,Seeed Studio,,hand
2,"U2,U3",AL8860WT-7,TSOT-23-5,AL8860WT-7,Diodes Inc,C125330,JLCPCB

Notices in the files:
parts and their libraries:
Seeed XIAO ESP32C3, castellated edge pads only (1-14). Pad geometry from Seeed OPL_Kicad_Library XIAO-ESP32-C3-SMD (commit b0035c5, CC BY-SA 4.0). Underside pads (JTAG, EN, VBAT) deliberately omitted: keep copper and vias out from under the module.
